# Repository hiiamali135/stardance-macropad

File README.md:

# stardance-macropad
Custom Macro pad with 6 keys and 2 rotary encoders.
Designed in KiCad
PCB Dimentions: 67.5mm x 69.0mm

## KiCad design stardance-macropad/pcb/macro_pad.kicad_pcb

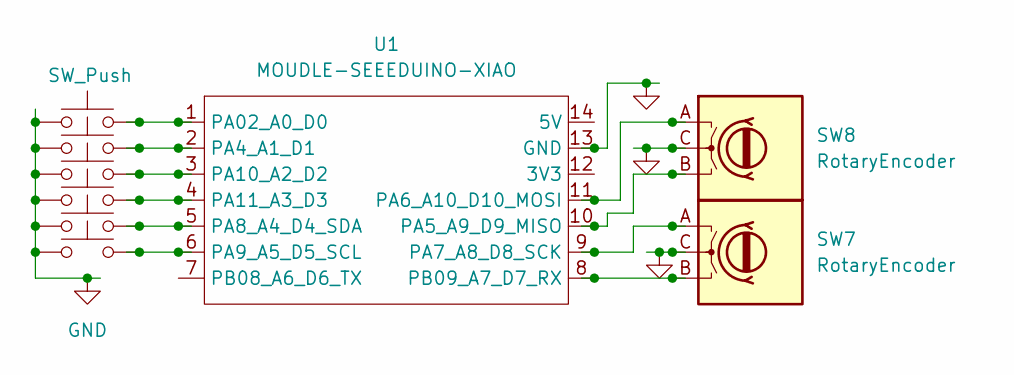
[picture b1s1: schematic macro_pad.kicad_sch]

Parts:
SW1, SW2, SW4, SW5, SW6, SW9: SW_Push; SW_Cherry_MX_1.00u_PCB
SW7, SW8: RotaryEncoder; RotaryEncoder_Alps_EC11E-Switch_Vertical_H20mm
U1: MOUDLE-SEEEDUINO-XIAO; XIAO-Generic-Hybrid-14P-2.54-21X17.8MM

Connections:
GND: SW1.1, SW2.1, SW4.1, SW5.1, SW6.1, SW7.C, SW8.C, SW9.1, U1.13 (GND)
unnamed: SW1.2, U1.1 (PA02_A0_D0)
unnamed: SW4.2, U1.2 (PA4_A1_D1)
unnamed: SW8.B, U1.10 (PA5_A9_D9_MISO)
unnamed: SW8.A, U1.11 (PA6_A10_D10_MOSI)
unnamed: SW7.A, U1.9 (PA7_A8_D8_SCK)
unnamed: SW6.2, U1.5 (PA8_A4_D4_SDA)
unnamed: SW9.2, U1.6 (PA9_A5_D5_SCL)
unnamed: SW5.2, U1.3 (PA10_A2_D2)
unnamed: SW2.2, U1.4 (PA11_A3_D3)
unnamed: SW7.B, U1.8 (PB09_A7_D7_RX)

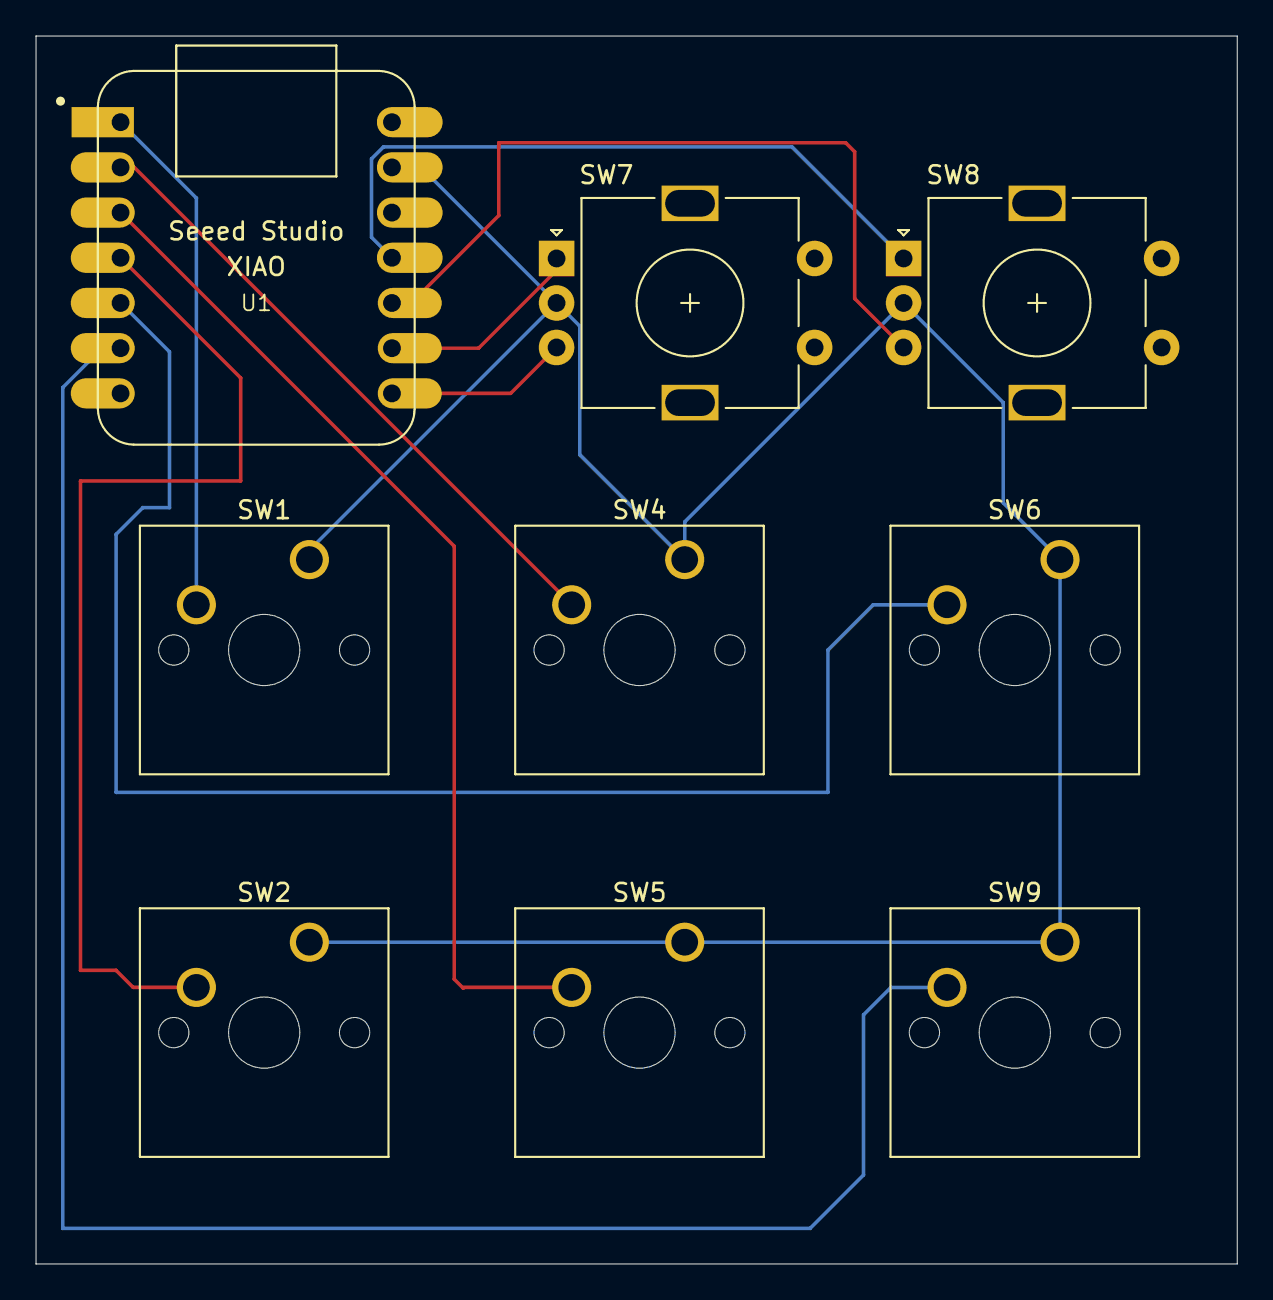
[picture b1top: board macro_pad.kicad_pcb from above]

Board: 2 copper layers, 67.5 x 69.0 mm, 9 parts (0 on the bottom side), 11 nets.

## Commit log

2026-06-18 Add design details and dimensions to README
